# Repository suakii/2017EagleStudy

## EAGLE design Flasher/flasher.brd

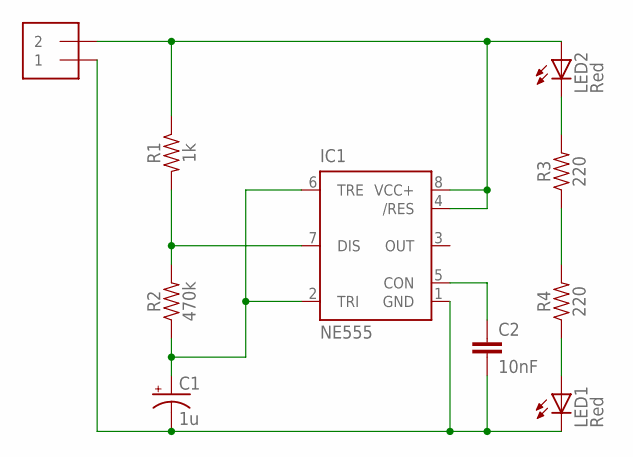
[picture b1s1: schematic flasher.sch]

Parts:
C1: 1u; CPOL-RADIAL-2.5MM-5MM
C2: 10nF; CAP-PTH-10MM
IC1: NE555; DIL-08
J1: 1X2-3.5MM
LED1, LED2: Red; LED5MM
R1: 1k; AXIAL-0.3
R2: 470k; AXIAL-0.3
R3, R4: 220; AXIAL-0.3

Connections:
GND: C1.2 (-), C2.2, IC1.1 (GND), J1.1, LED1.K (C)
unnamed: IC1.7 (DIS), R1.P$2 (2), R2.P$2 (2)
unnamed: C1.1 (+), IC1.2 (TRI), IC1.6 (TRE), R2.P$1 (1)
unnamed: LED1.A, R4.P$1 (1)
unnamed: R3.P$1 (1), R4.P$2 (2)
unnamed: LED2.K (C), R3.P$2 (2)
unnamed: C2.1, IC1.5 (CON)
VCC+: IC1.4 (/RES), IC1.8 (VCC+), J1.2, LED2.A, R1.P$1 (1)

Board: 2 copper layers, 10 parts (0 on the bottom side), 8 nets, no tracks yet.

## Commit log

2017-12-05 Flasher

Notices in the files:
parts and their libraries:
SparkFun-Capacitors: Licensing: Creative Commons ShareAlike 4.0 International - https://creativecommons.org/licenses/by-sa/4.0
